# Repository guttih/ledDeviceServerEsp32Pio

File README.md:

# ledDeviceServerEsp32Pio
An application running on esp32 which controls a addressable light strip using
the [fastLed] library.  Supported strips are WS2811, WS2801 and  APA102.

A new program can be uploaded over the air (OTA) and controlled using [VoffCon].

## Pins
__GPIO16__ is connected to DI or Data on the strip and if the strip has
a clock pin then __GPIO17__ is connected to thi CL or Clock pin.

Some older projects use the GPIO13 and GPIO14 pins, but these pins ADC2 which
are used by the Wifi library and should not be used with wifi. 

## Development

For information intended for development of this project can be found in the
[development.adoc](docs/development.adoc) document.

[fastLed]: https://fastled.io/
[VoffCon]: http://voffcon.com/

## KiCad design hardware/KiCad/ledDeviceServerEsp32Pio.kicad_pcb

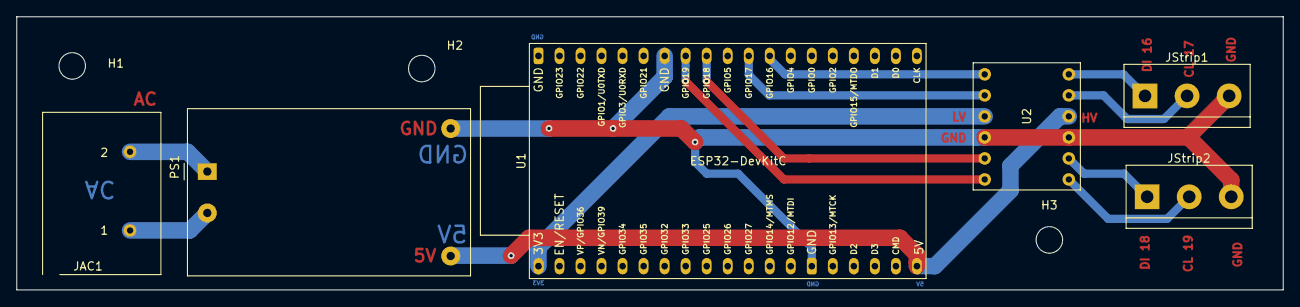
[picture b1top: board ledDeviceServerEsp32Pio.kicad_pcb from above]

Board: 2 copper layers, 153.0 x 33.0 mm, 9 parts (0 on the bottom side), 13 nets.

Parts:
H1, H2, H3: MountingHole; MountingHole_3.2mm_M3
JAC1: Terminal_AC; Screw_Termianl_01x02
JStrip1, JStrip2: Terminal_LCDstrip; TerminalBlock_bornier-3_P5.08mm
PS1: HLK-PM01; Converter_ACDC_HiLink_HLK-PMxx
U1: ESP32-DevKitC
U2: LLC_4CH

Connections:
/CLOCK1: JStrip1.2, U2.7
/CLOCK2: JStrip2.2, U2.11
/DATA1: JStrip1.1, U2.5
/DATA2: JStrip2.1, U2.9
GND: JStrip1.3, JStrip2.3, PS1.3, U1.14, U1.32, U2.3
unnamed: JAC1.1, PS1.2
unnamed: JAC1.2, PS1.1
unnamed: PS1.4, U1.19, U2.2
unnamed: U1.1, U2.1
unnamed: U1.27, U2.4
unnamed: U1.28, U2.6
unnamed: U1.30, U2.8
unnamed: U1.31, U2.10

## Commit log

2021-10-07 gitIgnoring the wifipassword
2021-10-07 whaat
2021-10-07 untracking config.h
2021-10-07 Activating upload program wirelessly (OTA)
2021-10-07 Reducing flickering because of ArduinoOTA.handle
2021-11-17 adding README.md
2021-11-17 Adding Hardware folder for KiCad Project
2021-11-17 changing datapin on Chrismas strip to 16
2021-11-17 Adding programFire
2021-11-18 KiCad Schematic done
2021-11-18 removing file ledDeviceServerEsp32Pio-cache.lib
2021-11-18 .gitignoring *-cache.lib
2021-11-18 pcb done
2021-11-23 Printed one board
2021-11-25 drawing and wiring
2021-12-02 not allowing the strip to turn off when wifi is lost
2021-12-24 Adding text on plugs
2021-12-24 This was produced, zipped and sent to jlcpcb.com
2023-02-18 adding long-pcb
2023-02-18 adding hostname and reconnection refinement
2023-02-19 Working on ORRI strip
2023-02-19 Fixing hostname
2023-02-19 removing printHeapSize
2023-02-19 setDirection should return a value
2023-02-19 example upload from linux
2023-02-22 Adding Inheritance to instead of IFDEFS
2023-02-22 Classes StripOrri and StripSoley now extend StripHelper
2023-02-22 fixing hostname in orri
2023-09-03 setting maximum power to 5v and 7amps
2024-07-25 adding partfinder2
